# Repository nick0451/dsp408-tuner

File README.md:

# DSP-408 Automated Tuner

Automated acoustic tuning for the **Dayton Audio DSP-408** (4-in / 8-out car audio DSP).

Plays measurement stimuli through the system, captures them with calibrated microphones, derives impulse and frequency responses, fits corrections (gain, delay, crossover, parametric EQ) against a target curve and the chip's resource budget, writes them to the DSP, and re-measures to verify convergence.

This is a measurement and constrained-optimization system. There are no learned components in the tuning path.

## Status

**See [docs/STATE.md](docs/STATE.md) for current state and next steps.**

| Milestone | Scope | State |
|---|---|---|
| M0 | DSP-408 control protocol | **Done.** Decoded; all parameter scalings measured; codec *and session layer* validated against real device traffic |
| M1 | Measurement engine | **Done**, and validated against REW — 0.35 dB max / 0.09 rms over 30 Hz—3.5 kHz, a second implementation sharing no code |
| M2 | Microphone calibration rig | Not started |
| M3 | DSP control backend | **Done, and proven through Stage 6 on hardware.** 2026-08-11: reads the real device clean — 31/31 transactions, firmware `MYDW-AV1.06`, all eight channel records — survives 120 s of link silence, and writes: a fragmented no-op, a real change with verified rollback, then **46 writes across 4 channels** including the backend's own multi-block `write_channel` and a gang write read back holding one tune. Still unproven: preset-recall restore, all eight channels in one run, and writing while audio plays |
| M4 | Closed tuning loop | **Ran end to end on hardware 2026-08-12 and accepted.** `tuner.orchestrate` joins the parts — arm, floor, baseline, fit, write once, verify, settle — with a fingerprinted objective, per-output budgets, driver gangs and acoustically-verified rollback, on an electrical bench rig with the device restored and verified byte-identical afterwards. Rehearsed against the fake through every outcome. Remaining: no microphone has been in the loop, all eight channels in one run, and writing while audio plays |

In place: the measurement signal chain (sweep, deconvolution, gating,
frequency/phase/RT60, spatial averaging, REW cal files), an end-to-end capture
path with safety ramping and provenance, rig verification, the safety limiter,
the improvement invariant, the DSP backend interface with a resource-budget
simulator, a wire-protocol codec **validated byte-for-byte against captured
device traffic**, readers for the vendor backup format and for Android HCI
snoop logs, and a PEQ fitter that solves on the device's real parameter grids.

**This code reads, writes, tunes and rolls back a real DSP-408.** Proven on
hardware through every bring-up stage and a full closed-loop run on
2026-08-12, with the device verified byte-identical afterwards each time.
No microphone has been in the loop yet -- the closed loop ran electrically,
DSP output into a line input.

Also in place as of 2026-08-09: the full DSP control stack — framing, a
transmit allow-list, transports, an in-process fake device, lock-step sessions,
read-modify-write with a journal, and **snapshot/restore, so rollback is now a
mechanism rather than a policy**. Plus target curves, time alignment, and a
bring-up rehearsal that runs the entire first-contact procedure against the fake
including every abort path.

Added by the 2026-08-09 bench session: **preset store and recall**, which is
the device-side rollback the improvement invariant has always described. A
recall turns out to be eight *reads* with the slot in a header field — no
select opcode — which also means a frame that looks like an ordinary read
replaces the entire working tune. The transmit policy had been permitting it.

That session also mapped the crossover slope and alignment bytes and the EQ
band-type byte, all three of which had read as constants on all 112 stored
channel-records. They were not opaque: **the corpus simply had no variation in
them**, because every tune ever saved was Linkwitz-Riley, at 12 or 24 dB per
octave, with no shelves. Sixteen deliberate A/Bs settled what no further
analysis of the backups could have.

Still stubbed: `tuner.audio.devices` and everything in M2.

**Every validation claim here names its reference and its independence.** The
wire protocol and the 296-byte channel readback are checked against evidence
from outside this project — 61 742 frames of captured vendor traffic, and
the vendor app's own backup files. The measurement engine is checked against
REW, an implementation sharing no code with it, over the band where the
*reference* is repeatable enough to serve as one; above 3.5 kHz REW's own
run-to-run scatter (0.370 dB rms) exceeds our disagreement with it, and our
engine repeats to 0.080. See the validation policy in
[CLAUDE.md](CLAUDE.md).

## Install

```bash
pip install -e ".[dev]"
pytest
```

The test suite passes with no audio hardware attached and no DSP connected.

## Hardware

The DSP-408 contains **two** Analog Devices ADAU1701 SigmaDSPs — 48 kHz fixed, 1024 program instructions each, and delay RAM pooled per chip rather than globally. The optimizer treats those limits as hard constraints. Control is over **classic Bluetooth RFCOMM (SPP)** — measured from a capture of the vendor app, correcting an earlier and wrong conclusion that it was BLE. The wire protocol is decoded, implemented in `tuner.dsp.protocol`, and validated against that capture.

See [docs/hardware.md](docs/hardware.md) for the host platform decision, bill of materials, and measured rig characterization. Short version: an N100-class x86 mini-PC with an external class-compliant USB interface. Compute is not the constraint in this project; audio I/O reliability and microphone calibration are.

The four-microphone interface is being **built rather than bought** — see [docs/measurement-interface.md](docs/measurement-interface.md). Commercial multichannel interfaces all carry gain knobs, which turn a provenance field into a remembered number, and none can offer an internal loopback. Measurements today run on a Focusrite Scarlett Solo, and will continue to until the new rig reproduces its results.

## Documentation

- [docs/STATE.md](docs/STATE.md) — **current state, open questions, next steps**
- [CLAUDE.md](CLAUDE.md) — safety rules, unit conventions, hardware constraints
- [docs/hardware.md](docs/hardware.md) — platform, BOM, wiring
- [docs/measurement-interface.md](docs/measurement-interface.md) — the 4-mic interface design and why it is built, not bought
- [docs/measurement-theory.md](docs/measurement-theory.md) — swept-sine method and its limits
- [docs/dsp408-protocol.md](docs/dsp408-protocol.md) — decoded control protocol, its derivation, and the transport/session/scaling measurements
- [docs/board-probing.md](docs/board-probing.md) — what is on the boards, and how to probe them
- [docs/next-bench-session.md](docs/next-bench-session.md) — run sheet for the next hardware session
- [docs/review-2026-08-09.md](docs/review-2026-08-09.md) — adversarial review scorecard, including the claims that were wrong
- [docs/safety.md](docs/safety.md) — why each safety rule exists

## Safety

Measurement sweeps can destroy drivers. Every stimulus passes through `tuner.safety`, starts at −30 dBFS and ramps, and aborts on clipping or DC offset. Channels whose crossover is unknown are treated as tweeters. These rules have no exceptions — see [docs/safety.md](docs/safety.md).

One limit of that limiter is worth stating on the front page: **it caps what we transmit, not what the driver receives.** The DSP's own channel gain and EQ boost are applied downstream of everything this code controls, so a +12 dB band turns a −18 dBFS stimulus into 0 dBFS at the speaker. Subtract the device's gain from the stimulus deliberately.

Writing to the DSP carries its own hazards, because **every write is immediately non-volatile and the device has no undo**. The backend refuses anything the vendor app was never observed doing, caps how many channels one session can touch, requires a verified snapshot on disk before it will write at all, and verifies every write by reading the whole 296-byte channel back. `python tools/dsp408_probe.py rehearse` runs that entire procedure against an in-process fake, including every abort path, before it meets hardware.

## License

MIT — see [LICENSE](LICENSE).

The protocol findings in `docs/` are the result of black-box measurement and
of decoding this project's own captures of the device's traffic. No vendor
source or firmware is redistributed here.

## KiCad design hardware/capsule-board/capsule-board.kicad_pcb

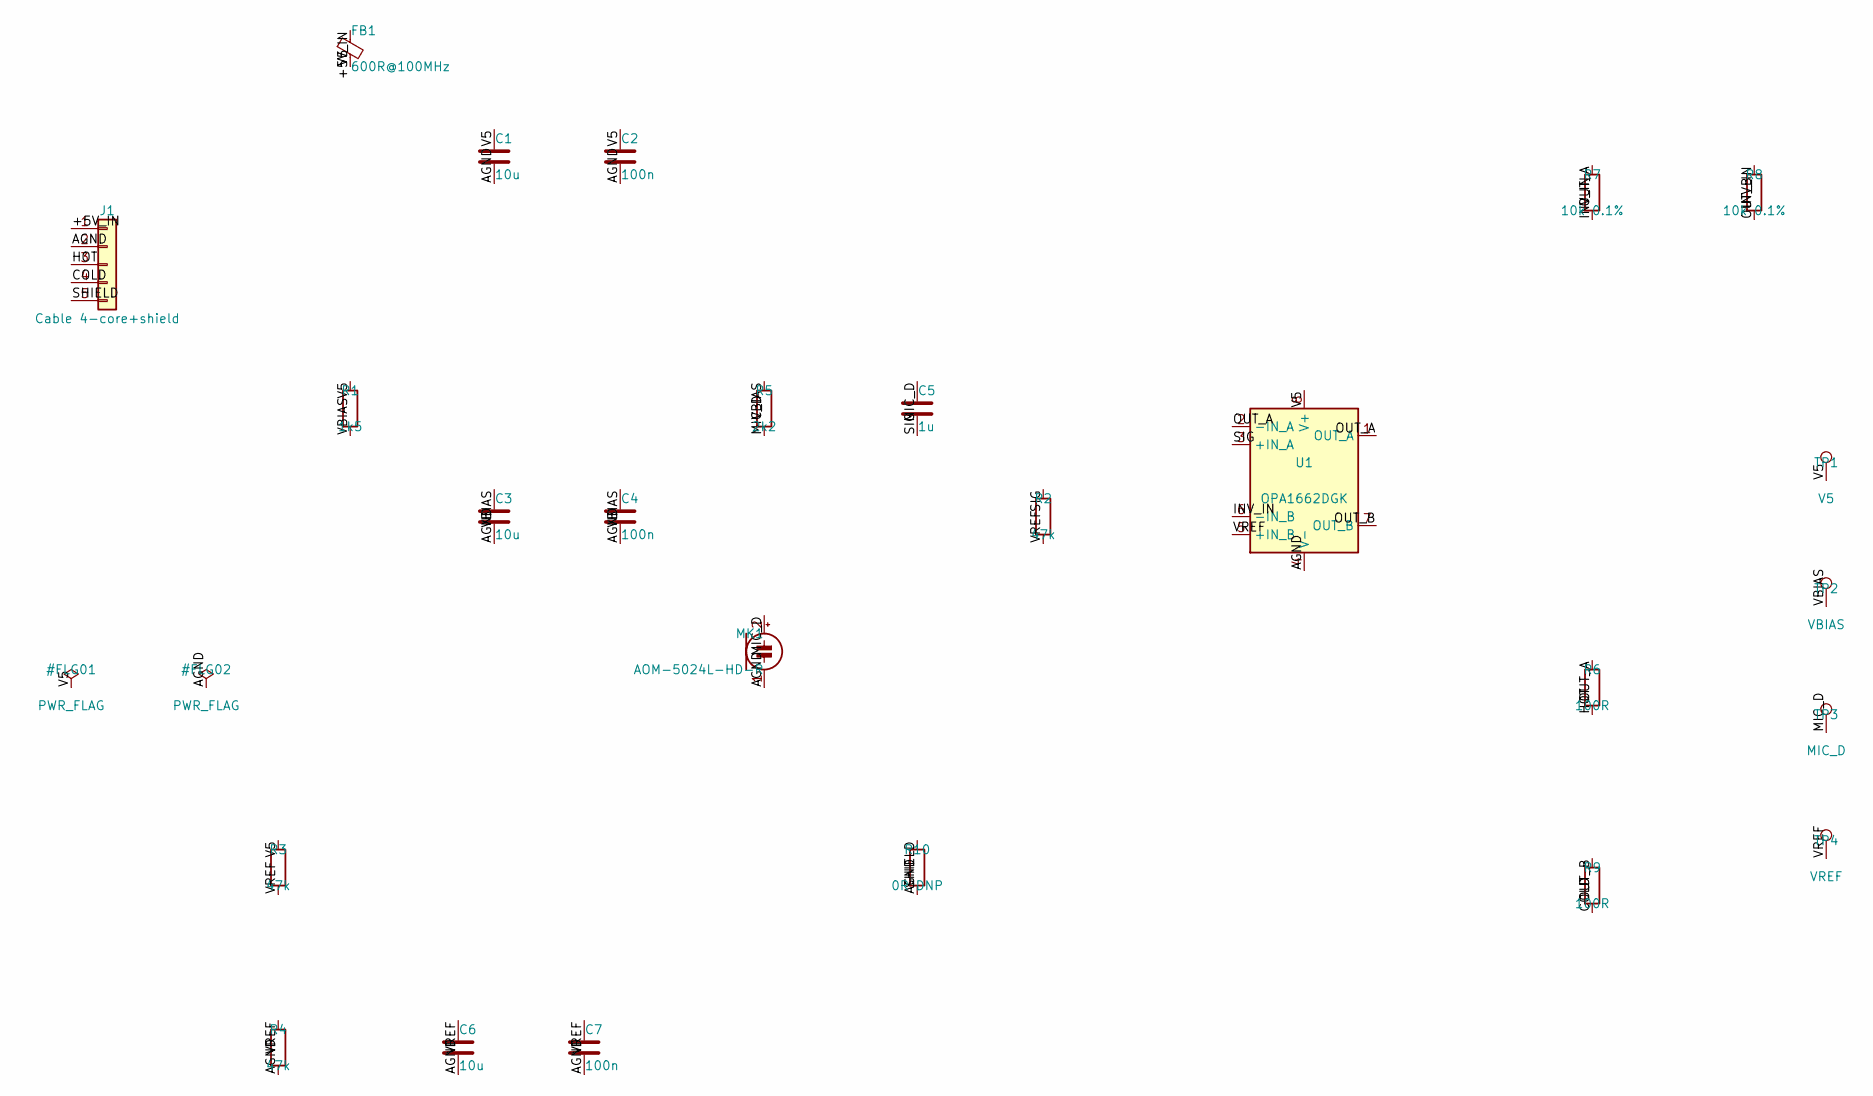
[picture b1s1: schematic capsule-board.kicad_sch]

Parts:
C1, C3, C6: 10u; C_0805_2012Metric
C2, C4, C7: 100n; C_0603_1608Metric
C5: 1u; C_0805_2012Metric
FB1: 600R@100MHz; L_0603_1608Metric
J1: Cable 4-core+shield; CablePads_1x05_P1.50mm
MK1: AOM-5024L-HD-R; MicCapsule_AOM5024L_2Pad_THT
R1: 1k5; R_0603_1608Metric
R2, R3, R4: 47k; R_0603_1608Metric
R5: 2k2; R_0603_1608Metric
R6, R9: 100R; R_0603_1608Metric
R7, R8: 10k 0.1%; R_0603_1608Metric
R10: 0R DNP; R_0603_1608Metric
TP1: V5; TestPoint_Pad_D1.5mm
TP2: VBIAS; TestPoint_Pad_D1.5mm
TP3: MIC_D; TestPoint_Pad_D1.5mm
TP4: VREF; TestPoint_Pad_D1.5mm
U1: OPA1662DGK; MSOP-8_3x3mm_P0.65mm

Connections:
/+5V_IN: FB1.1, J1.1
/AGND: C1.2, C2.2, C3.2, C4.2, C6.2, C7.2, J1.2, MK1.1 (-), R4.2, R10.2, U1.4 (V-)
/COLD: J1.4, R9.2
/HOT: J1.3, R6.2
/INV_IN: R7.2, R8.1, U1.6 (-IN_B)
/MIC_D: C5.1, MK1.2 (+), R5.2, TP3.1
/OUT_A: R6.1, R7.1, U1.1 (OUT_A), U1.2 (-IN_A)
/OUT_B: R8.2, R9.1, U1.7 (OUT_B)
/SHIELD: J1.5, R10.1
/SIG: C5.2, R2.1, U1.3 (+IN_A)
/V5: C1.1, C2.1, FB1.2, R1.1, R3.1, TP1.1, U1.8 (V+)
/VBIAS: C3.1, C4.1, R1.2, R5.1, TP2.1
/VREF: C6.1, C7.1, R2.2, R3.2, R4.1, TP4.1, U1.5 (+IN_B)

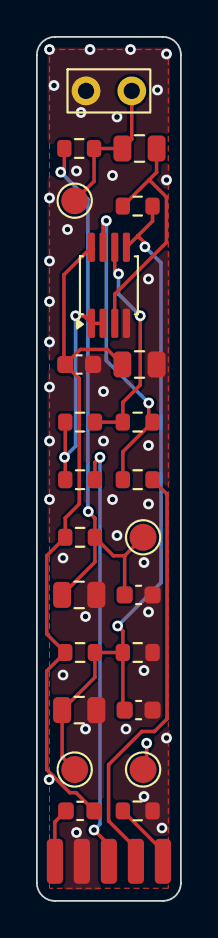
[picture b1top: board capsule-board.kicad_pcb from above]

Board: 4 copper layers, 8.0 x 48.0 mm, 25 parts (0 on the bottom side), 13 nets.

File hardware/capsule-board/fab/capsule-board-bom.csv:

"Reference","Value","Footprint","QUANTITY"
"C1,C3,C6","10u","Capacitor_SMD:C_0805_2012Metric","3"
"C2,C4,C7","100n","Capacitor_SMD:C_0603_1608Metric","3"
"C5","1u","Capacitor_SMD:C_0805_2012Metric","1"
"FB1","600R@100MHz","Inductor_SMD:L_0603_1608Metric","1"
"J1","Cable 4-core+shield","capsule-board:CablePads_1x05_P1.50mm","1"
"MK1","AOM-5024L-HD-R","capsule-board:MicCapsule_AOM5024L_2Pad_THT","1"
"R1","1k5","Resistor_SMD:R_0603_1608Metric","1"
"R2-R4","47k","Resistor_SMD:R_0603_1608Metric","3"
"R5","2k2","Resistor_SMD:R_0603_1608Metric","1"
"R6,R9","100R","Resistor_SMD:R_0603_1608Metric","2"
"R7,R8","10k 0.1%","Resistor_SMD:R_0603_1608Metric","2"
"R10","0R DNP","Resistor_SMD:R_0603_1608Metric","1"
"TP1","V5","TestPoint:TestPoint_Pad_D1.5mm","1"
"TP2","VBIAS","TestPoint:TestPoint_Pad_D1.5mm","1"
"TP3","MIC_D","TestPoint:TestPoint_Pad_D1.5mm","1"
"TP4","VREF","TestPoint:TestPoint_Pad_D1.5mm","1"
"U1","OPA1662DGK","Package_SO:MSOP-8_3x3mm_P0.65mm","1"
